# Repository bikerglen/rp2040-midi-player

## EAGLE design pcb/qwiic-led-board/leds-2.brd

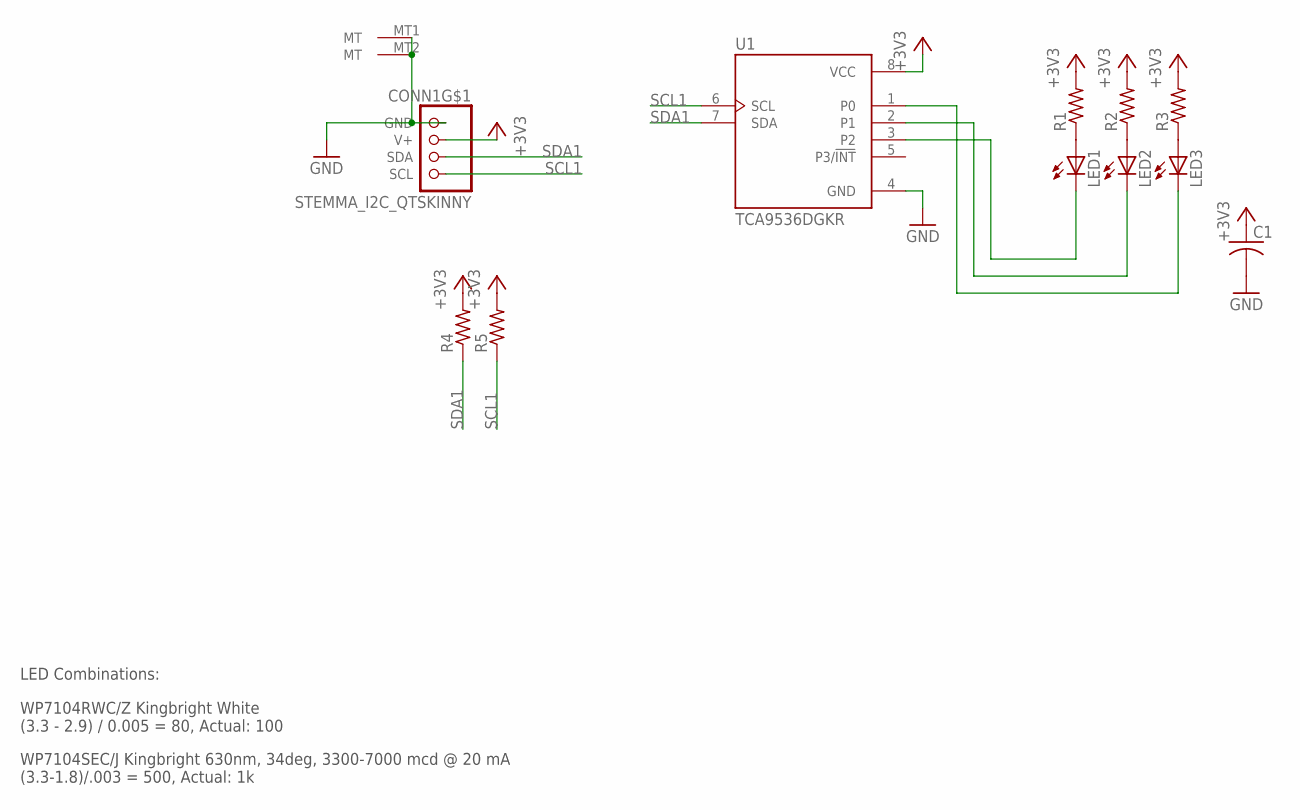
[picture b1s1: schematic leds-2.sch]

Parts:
C1: C-USC0603K; C0603K
CONN1: STEMMA_I2C_QTSKINNY; JST_SH4_SKINNY
LED1, LED2, LED3: LED3MM
R1, R2, R3, R4, R5: R-US_R0603; R0603
U1: TCA9536DGKR; SOP65P490X110-8N

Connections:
+3V3: C1.1, CONN1.2 (V+), R1.2, R2.2, R3.2, R4.2, R5.2, U1.8 (VCC)
GND: C1.2, CONN1.1 (GND), CONN1.MT1 (MT), CONN1.MT2 (MT), U1.4 (GND)
unnamed: LED3.K (C), U1.1 (P0)
unnamed: LED2.K (C), U1.2 (P1)
unnamed: LED1.K (C), U1.3 (P2)
unnamed: LED1.A, R1.1
unnamed: LED2.A, R2.1
unnamed: LED3.A, R3.1
SCL1: CONN1.4 (SCL), R5.1, U1.6 (SCL)
SDA1: CONN1.3 (SDA), R4.1, U1.7 (SDA)

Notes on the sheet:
LED Combinations:
WP7104RWC/Z Kingbright White (3.3 - 2.9) / 0.005 = 80, Actual: 100
WP7104SEC/J Kingbright 630nm, 34deg, 3300-7000 mcd @ 20 mA (3.3-1.8)/.003 = 500, Actual: 1k

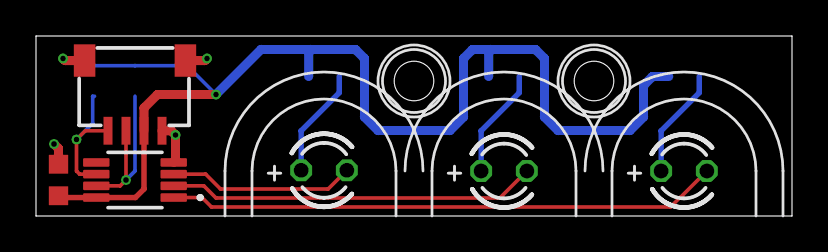
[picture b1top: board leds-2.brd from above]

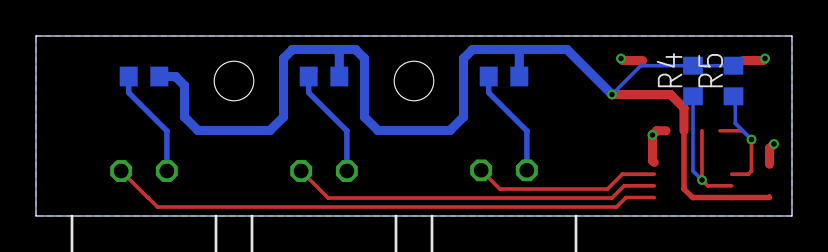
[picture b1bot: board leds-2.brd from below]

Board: 2 copper layers, 42.0 x 10.0 mm, 11 parts (5 on the bottom side), 10 nets.

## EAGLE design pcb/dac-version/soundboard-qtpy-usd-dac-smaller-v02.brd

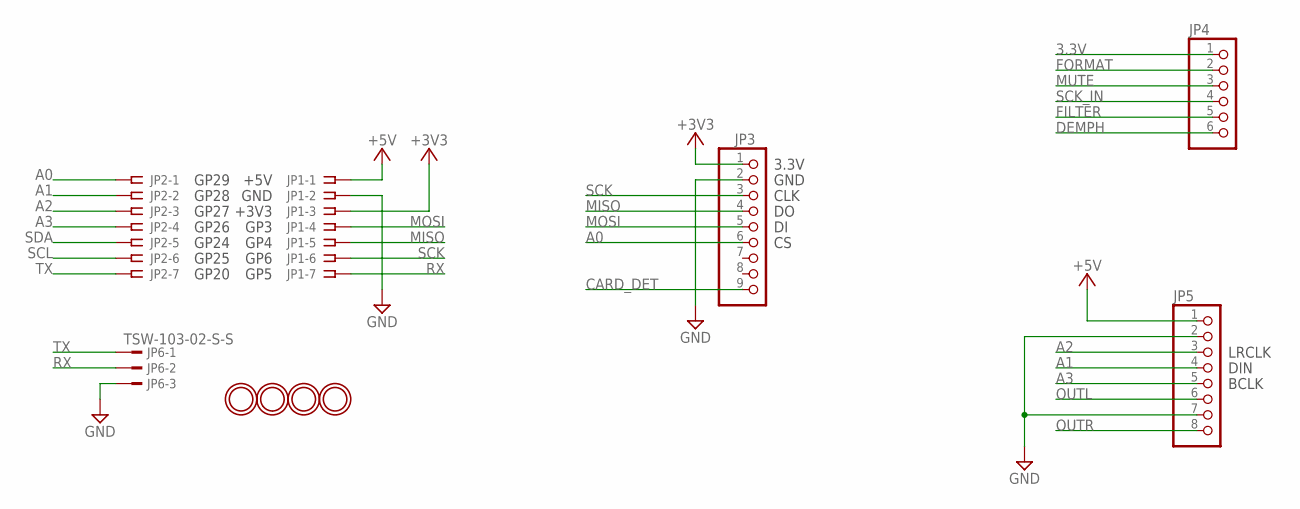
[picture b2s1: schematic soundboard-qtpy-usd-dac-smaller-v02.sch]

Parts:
JP1, JP2: SSW-107-02-S-S
JP3: HEADER-1X970MIL; 1X09_ROUND_70
JP4: HEADER-1X670MIL; 1X06_ROUND_70
JP5: HEADER-1X8ROUND; 1X08_ROUND
JP6: TSW-103-02-S-S
U$11, U$12, U$13, U$14: MOUNTINGHOLE2.5; MOUNTINGHOLE_2.5_PLATED

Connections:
3.3V: JP4.1
+3V3: JP1.3, JP3.1
+5V: JP1.1, JP5.1
A0: JP2.1, JP3.6
A1: JP2.2, JP5.4
A2: JP2.3, JP5.3
A3: JP2.4, JP5.5
CARD_DET: JP3.9
DEMPH: JP4.6
FILTER: JP4.5
FORMAT: JP4.2
GND: JP1.2, JP3.2, JP5.2, JP5.7, JP6.3
MISO: JP1.5, JP3.4
MOSI: JP1.4, JP3.5
MUTE: JP4.3
OUTL: JP5.6
OUTR: JP5.8
RX: JP1.7, JP6.2
SCK: JP1.6, JP3.3
SCK_IN: JP4.4
SCL: JP2.6
SDA: JP2.5
TX: JP2.7, JP6.1

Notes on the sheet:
GND
+5V
GP29
GP28
GP27
+3V3
GP3
GP4
GP6
GP5
GP26
GP24
GP25
GP20
3.3V
CLK
LRCLK
DIN
BCLK

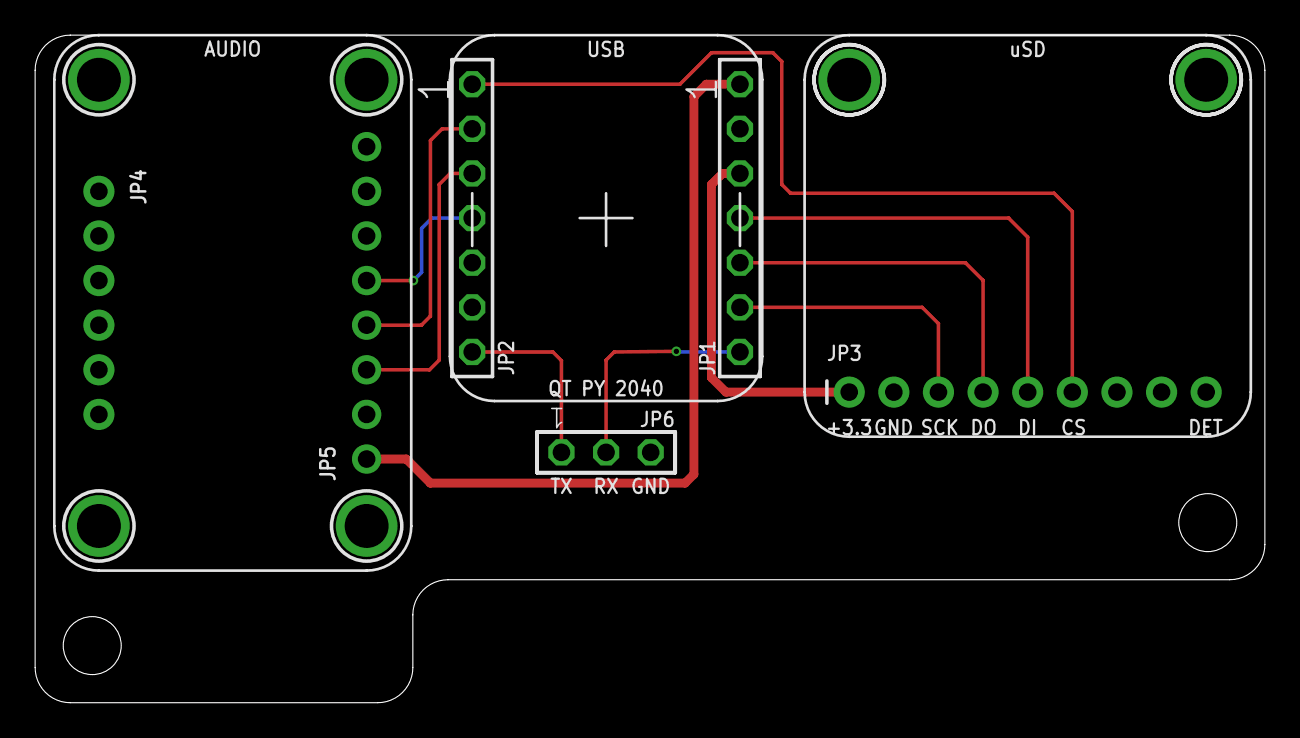
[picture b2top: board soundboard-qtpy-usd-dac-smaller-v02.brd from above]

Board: 2 copper layers, 70.0 x 38.0 mm, 26 parts (0 on the bottom side), 12 nets.

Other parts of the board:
PLABEL0: PLABEL0
PLABEL1: PLABEL1
PLABEL2: PLABEL2
PLABEL3: PLABEL3
PLABEL4: PLABEL4
PLABEL5: PLABEL5
PLABEL6: PLABEL6
PLABEL7: PLABEL7
PLABEL8: PLABEL8
PLABEL9: PLABEL9
PLABEL10: PLABEL10
PLABEL11: PLABEL11
PLABEL12: PLABEL12
PLABEL13: PLABEL13
U$1, U$2: MOUNTINGHOLE2.5; MOUNTINGHOLE_2.5_PLATED

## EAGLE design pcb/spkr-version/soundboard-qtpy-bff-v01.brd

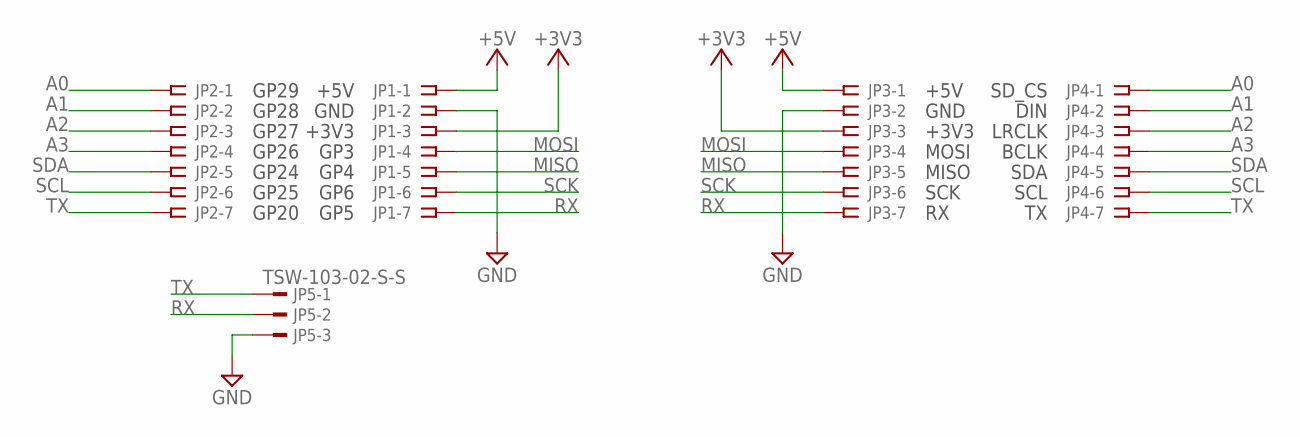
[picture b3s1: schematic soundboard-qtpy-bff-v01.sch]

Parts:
JP1, JP2, JP3, JP4: SSW-107-02-S-S
JP5: TSW-103-02-S-S

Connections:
+3V3: JP1.3, JP3.3
+5V: JP1.1, JP3.1
A0: JP2.1, JP4.1
A1: JP2.2, JP4.2
A2: JP2.3, JP4.3
A3: JP2.4, JP4.4
GND: JP1.2, JP3.2, JP5.3
MISO: JP1.5, JP3.5
MOSI: JP1.4, JP3.4
RX: JP1.7, JP3.7, JP5.2
SCK: JP1.6, JP3.6
SCL: JP2.6, JP4.6
SDA: JP2.5, JP4.5
TX: JP2.7, JP4.7, JP5.1

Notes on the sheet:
GND
+5V
GP29
GP28
GP27
+3V3
GP3
GP4
GP6
GP5
GP26
GP24
GP25
GP20
SD_CS
DIN
LRCLK
MOSI
MISO
SCK
BCLK
SDA
SCL

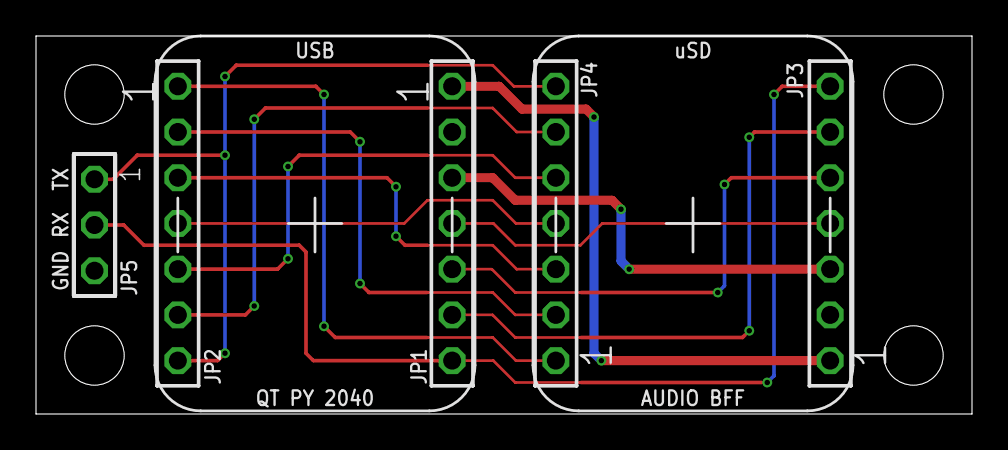
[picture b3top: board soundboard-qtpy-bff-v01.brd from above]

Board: 2 copper layers, 52.0 x 21.0 mm, 5 parts (0 on the bottom side), 14 nets.

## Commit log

2026-02-06 initial checkin
2026-02-06 add src directory and source code
2026-02-06 add basic build instructions
2026-02-06 formatting
2026-02-06 add pinout info
2026-02-06 fix tabs and spacing
2026-02-06 add tca9536-based i2c led status indicator code
2026-02-07 add speaker version design files, pdf, gerbers
2026-02-07 add pcb design files, pdf schematic, and gerbers
2026-02-07 add led board design files, schematic, and gerbers
2026-02-07 add enclosures for both speaker and dac versions
2026-02-07 fix paragraph ordering
2026-02-12 add i2c expander example
2026-02-12 minor fix
2026-02-12 add stand for midi fighter twister or midi fighter spectra
2026-02-13 increase board to board spacing from 7.5 to 8.0 mm
2026-02-13 add standoffs
2026-02-13 add 7.8 mm standoff plate
2026-02-13 remove 8 mm standoff
2026-02-18 add noise box 2000 enclosure for speaker version
2026-02-28 add support for rvone drum pad cat (no foot pedals yet)

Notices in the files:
parts and their libraries:
microbuilder: This work is placed in the public domain, and may be freely used for commercial and non-commercial work with the following conditions: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
